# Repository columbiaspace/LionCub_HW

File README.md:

# LionCub_HW
Hardware files for LionCub Satellite, Cubesat Team

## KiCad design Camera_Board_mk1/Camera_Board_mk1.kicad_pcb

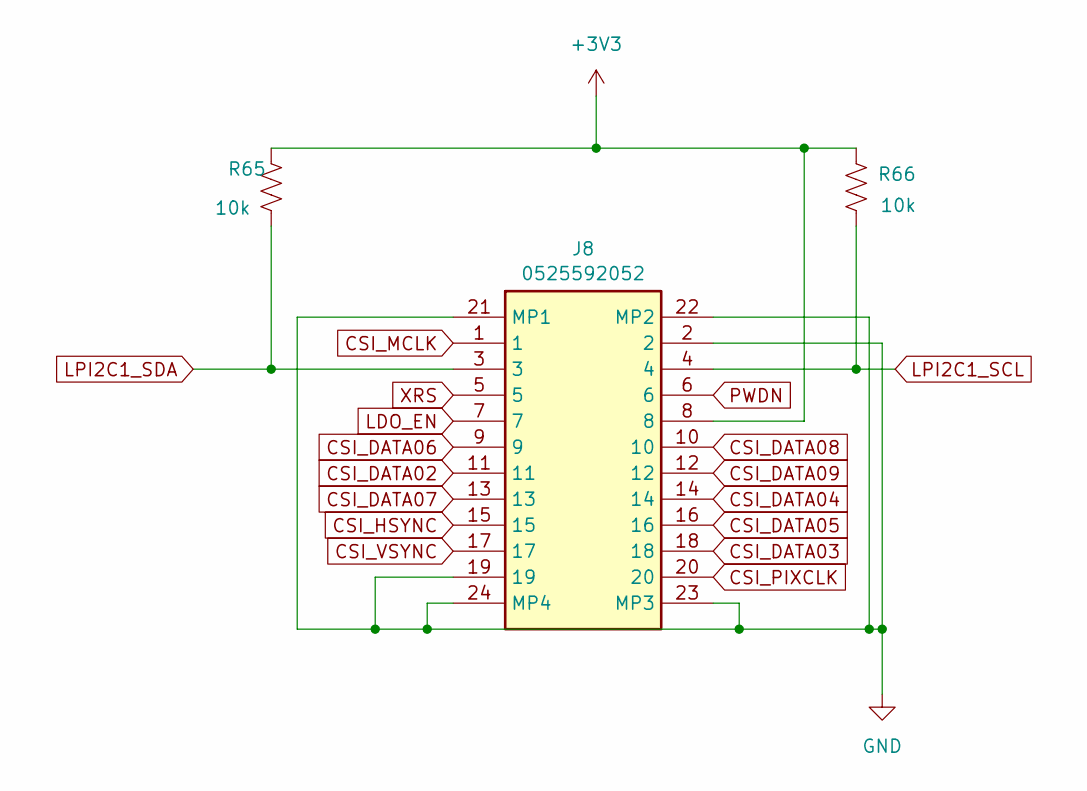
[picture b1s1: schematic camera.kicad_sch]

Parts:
J8: 0525592052; Manufacturer_Part_Number 0525592052‎
R65, R66: 10k; R_0201_0603Metric

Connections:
+3V3: J8.8, R65.1, R66.1; also elsewhere on the board
CSI_DATA02: J8.11; also elsewhere on the board
CSI_DATA03: J8.18; also elsewhere on the board
CSI_DATA04: J8.14; also elsewhere on the board
CSI_DATA05: J8.16; also elsewhere on the board
CSI_DATA06: J8.9; also elsewhere on the board
CSI_DATA07: J8.13; also elsewhere on the board
CSI_DATA08: J8.10; also elsewhere on the board
CSI_DATA09: J8.12; also elsewhere on the board
CSI_HSYNC: J8.15; also elsewhere on the board
CSI_MCLK: J8.1; also elsewhere on the board
CSI_PIXCLK: J8.20; also elsewhere on the board
CSI_VSYNC: J8.17; also elsewhere on the board
GND: J8.2, J8.19, J8.21 (MP1), J8.22 (MP2), J8.23 (MP3), J8.24 (MP4); also elsewhere on the board
LDO_EN: J8.7; also elsewhere on the board
LPI2C1_SCL: J8.4, R66.2; also elsewhere on the board
LPI2C1_SDA: J8.3, R65.2; also elsewhere on the board
PWDN: J8.6; also elsewhere on the board
XRS: J8.5; also elsewhere on the board

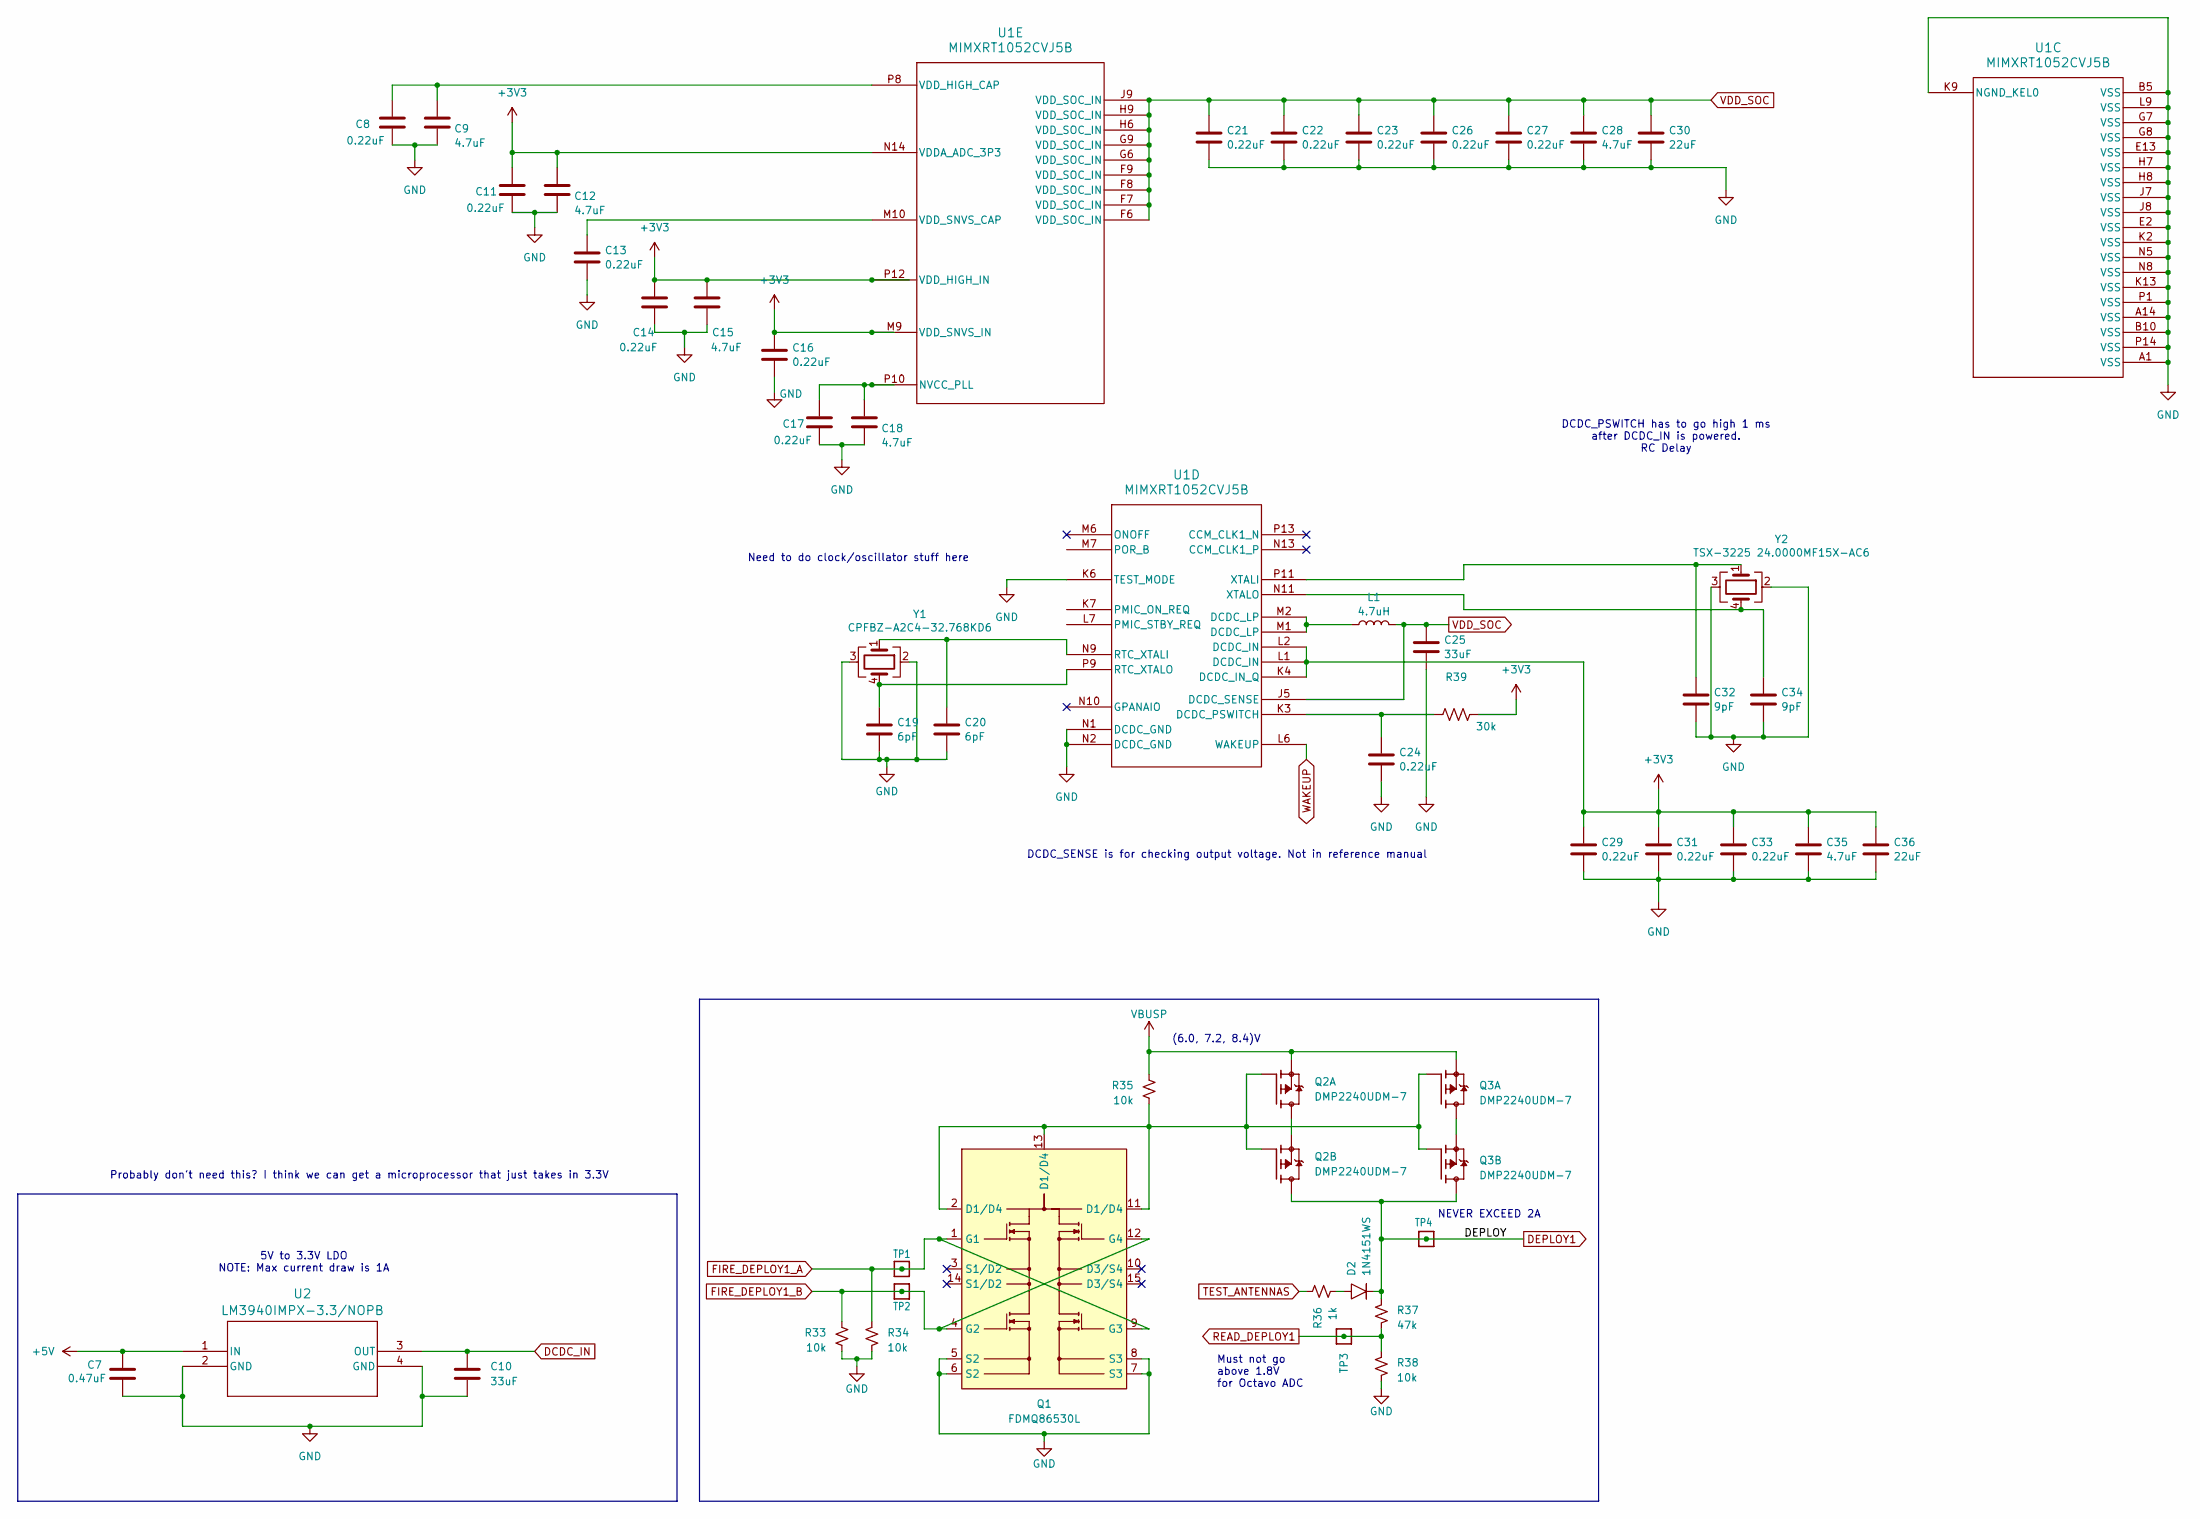
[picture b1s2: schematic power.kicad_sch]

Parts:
C7: 0.47uF; C_0201_0603Metric
C8, C11, C13, C14, C16, C17, C21, C22, C23, C24, C26, C27, C29, C31, C33: 0.22uF; C_0201_0603Metric
C9, C12, C15, C18, C28, C35: 4.7uF; C_0201_0603Metric
C10, C25: 33uF; C_0201_0603Metric
C19, C20: 6pF; C_0201_0603Metric
C30, C36: 22uF; C_0201_0603Metric
C32, C34: 9pF; C_0201_0603Metric
D2: 1N4151WS; D_SOD-323; MPN 1N4151WS-E3-08
L1: 4.7uH; L_0201_0603Metric
Q1: FDMQ86530L; FDMQ8203; MPN FDMQ86530L
Q2, Q3: DMP2240UDM-7; SOT-23-6; MPN DMP2240UDM-7
R33, R34, R35, R38: 10k; R_0201_0603Metric; MPN RMCF0603FT10K0
R36: 1k; R_0201_0603Metric; MPN RMCF0603FT1K00
R37: 47k; R_0201_0603Metric; MPN RMCF0603FT47K0
R39: 30k; R_0201_0603Metric
TP1, TP2, TP3, TP4: Test-Point; TestPoint_Pad_D1.0mm
U1: MIMXRT1052CVJ5B; BGA196C80P14X14_1200X1200X152
U2: LM3940IMPX-3.3/NOPB; MP04A
Y1: CPFBZ-A2C4-32.768KD6; Crystal_SMD_SeikoEpson_MC306-4Pin_8.0x3.2mm
Y2: TSX-3225 24.0000MF15X-AC6; Crystal_SMD_3225-4Pin_3.2x2.5mm

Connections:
+3V3: C11.1, C12.1, C14.1, C15.1, C16.1, C29.1, C31.1, C33.1, C35.1, C36.1, R39.2, U1.K4 (DCDC_IN_Q), U1.L1 (DCDC_IN), U1.L2 (DCDC_IN), U1.M9 (VDD_SNVS_IN), U1.N14 (VDDA_ADC_3P3), U1.P12 (VDD_HIGH_IN); also elsewhere on the board
DCDC_IN: C10.1, U2.3 (OUT); also elsewhere on the board
DEPLOY1: D2.1, Q2.4 (D), Q3.4 (D), R37.1, TP4.1; also elsewhere on the board
FIRE_DEPLOY1_A: Q1.1 (G1), Q1.9 (G3), R34.1, TP1.1; also elsewhere on the board
FIRE_DEPLOY1_B: Q1.4 (G2), Q1.12 (G4), R33.1, TP2.1; also elsewhere on the board
GND: C7.2, C8.2, C9.2, C10.2, C11.2, C12.2, C13.2, C14.2, C15.2, C16.2, C17.2, C18.2, C19.2, C20.2, C21.2, C22.2, C23.2, C24.2, C25.2, C26.2, C27.2, C28.2, C29.2, C30.2, C31.2, C32.2, C33.2, C34.2, C35.2, C36.2, Q1.5 (S2), Q1.6 (S2), Q1.7 (S3), Q1.8 (S3), R33.2, R34.2, R38.2, U1.A1 (VSS), U1.A14 (VSS), U1.B5 (VSS), U1.B10 (VSS), U1.E2 (VSS), U1.E13 (VSS), U1.G7 (VSS), U1.G8 (VSS), U1.H7 (VSS), U1.H8 (VSS), U1.J7 (VSS), U1.J8 (VSS), U1.K2 (VSS), U1.K6 (TEST_MODE), U1.K9 (NGND_KEL0), U1.K13 (VSS), U1.L9 (VSS), U1.N1 (DCDC_GND), U1.N2 (DCDC_GND), U1.N5 (VSS), U1.N8 (VSS), U1.P1 (VSS), U1.P14 (VSS), U2.2 (GND), U2.4 (GND), Y1.2, Y1.3, Y2.2, Y2.3; also elsewhere on the board
unnamed: D2.2, R36.2
unnamed: L1.1, U1.M1 (DCDC_LP), U1.M2 (DCDC_LP)
unnamed: Q2.2 (S), Q2.6 (D)
unnamed: Q1.2 (D1/D4), Q1.11 (D1/D4), Q1.13 (D1/D4), Q2.1 (G), Q2.3 (G), Q3.1 (G), Q3.3 (G), R35.2
unnamed: Q3.2 (S), Q3.6 (D)
unnamed: C24.1, R39.1, U1.K3 (DCDC_PSWITCH)
unnamed: C20.1, U1.N9 (RTC_XTALI), Y1.1
unnamed: C19.1, U1.P9 (RTC_XTALO), Y1.4
unnamed: C32.1, U1.P11 (XTALI), Y2.1
unnamed: C34.1, U1.N11 (XTALO), Y2.4
unnamed: C17.1, C18.1, U1.P10 (NVCC_PLL)
unnamed: C8.1, C9.1, U1.P8 (VDD_HIGH_CAP)
unnamed: C13.1, U1.M10 (VDD_SNVS_CAP)
READ_DEPLOY1: R37.2, R38.1, TP3.1; also elsewhere on the board
TEST_ANTENNAS: R36.1; also elsewhere on the board
VBUS: C7.1, U2.1 (IN); also elsewhere on the board
VBUSP: Q2.5 (S), Q3.5 (S), R35.1; also elsewhere on the board
VDD_SOC: C21.1, C22.1, C23.1, C25.1, C26.1, C27.1, C28.1, C30.1, L1.2, U1.F6 (VDD_SOC_IN), U1.F7 (VDD_SOC_IN), U1.F8 (VDD_SOC_IN), U1.F9 (VDD_SOC_IN), U1.G6 (VDD_SOC_IN), U1.G9 (VDD_SOC_IN), U1.H6 (VDD_SOC_IN), U1.H9 (VDD_SOC_IN), U1.J5 (DCDC_SENSE), U1.J9 (VDD_SOC_IN)
WAKEUP: U1.L6 (WAKEUP)

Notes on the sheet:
DCDC_SENSE is for checking output voltage. Not in reference manual
Need to do clock/oscillator stuff here
Probably don't need this? I think we can get a microprocessor that just takes in 3.3V
Must not go above 1.8V for Octavo ADC
DCDC_PSWITCH has to go high 1 ms after DCDC_IN is powered. RC Delay
5V to 3.3V LDO NOTE: Max current draw is 1A
NEVER EXCEED 2A
(6.0, 7.2, 8.4)V

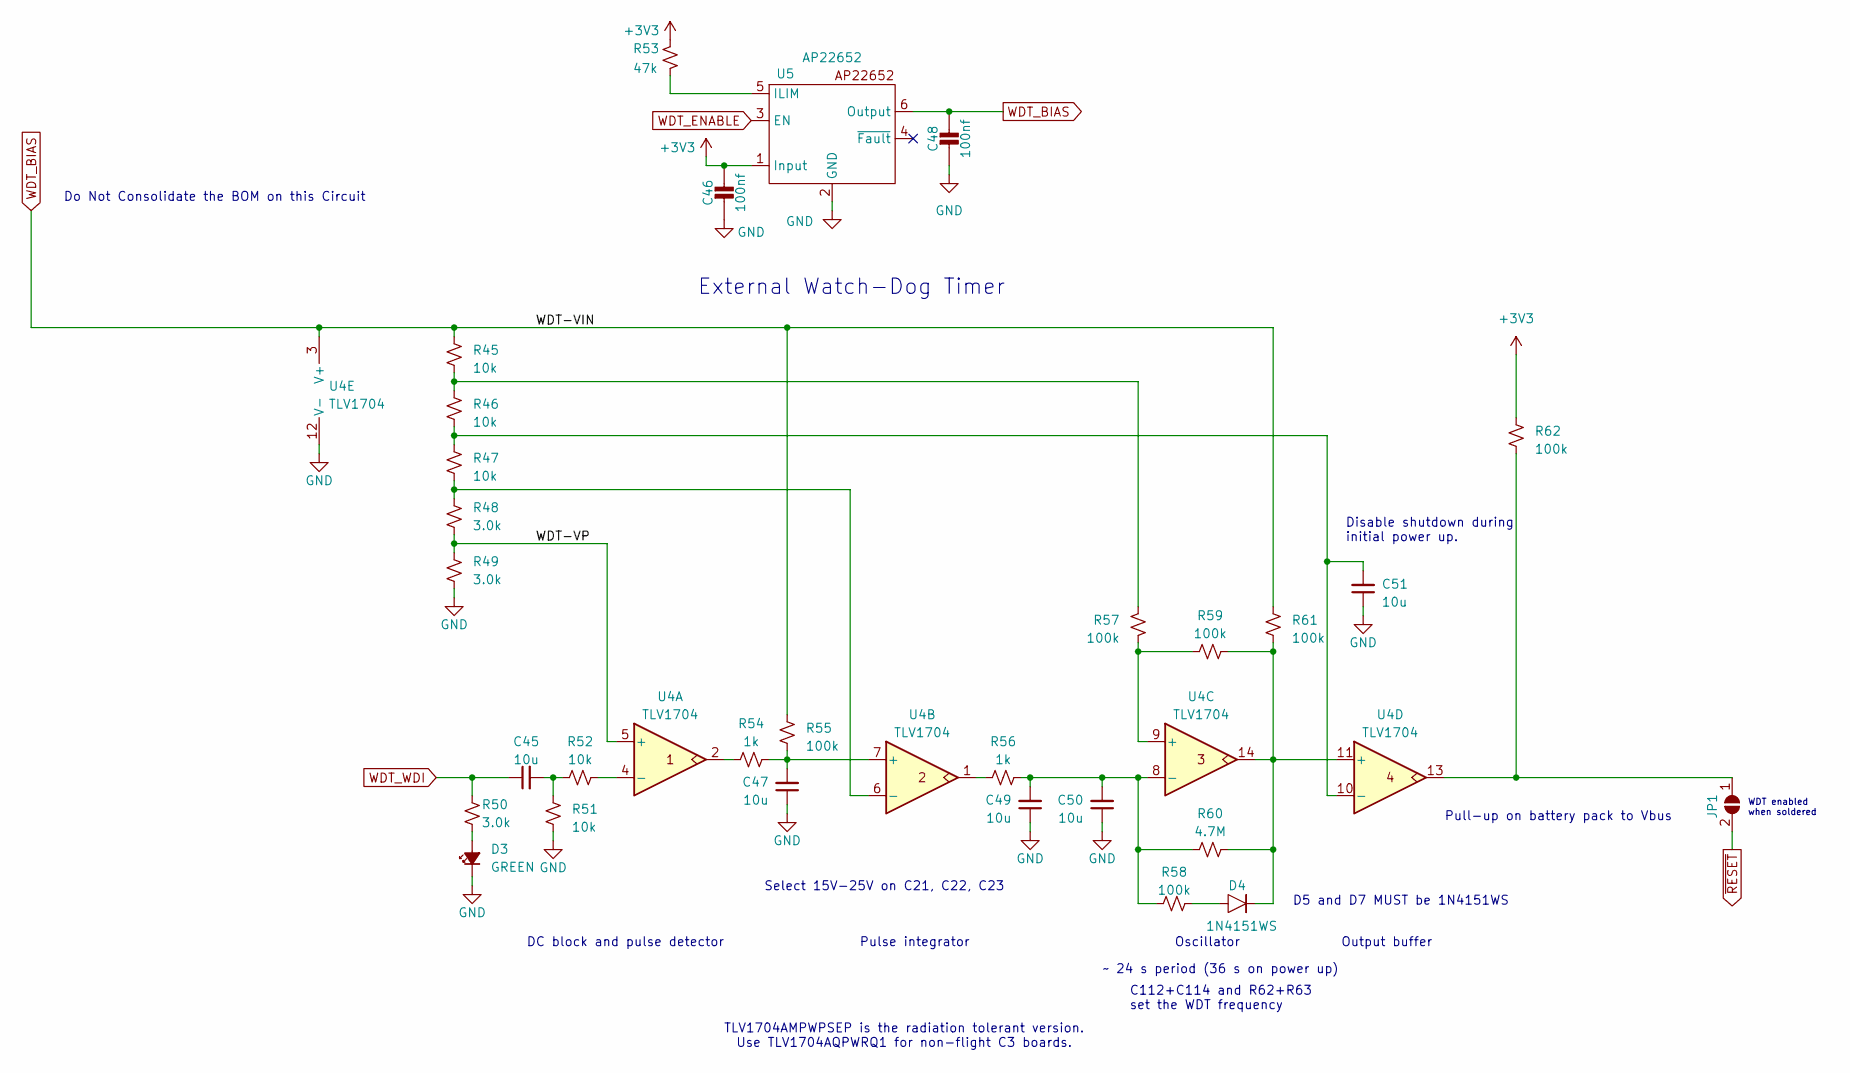
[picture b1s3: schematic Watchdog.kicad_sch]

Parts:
C45, C47, C49, C50, C51: 10u; C_0201_0603Metric; MPN GRT188R61C106KE13D
C46, C48: 100nf; C_0201_0603Metric
D3: GREEN; LED_0603_1608Metric; MPN 150060GS75000
D4: 1N4151WS; D_SOD-323; MPN 1N4151WS-E3-08
JP1: SolderJumper_2_Open; SolderJumper-2_P1.3mm_Open_RoundedPad1.0x1.5mm
R45, R46, R47, R51, R52: 10k; R_0201_0603Metric; MPN RMCF0603FT10K0
R48, R49, R50: 3.0k; R_0201_0603Metric; MPN RMCF0603FT3K00
R53: 47k; R_0201_0603Metric; MPN RMCF0603FT47K0
R54, R56: 1k; R_0201_0603Metric; MPN RMCF0603FT1K00
R55, R57, R58, R59, R61, R62: 100k; R_0201_0603Metric; MPN RMCF0603FT100K
R60: 4.7M; R_0201_0603Metric; MPN RMCF0603FT4M70
U4: TLV1704; TSSOP-14_4.4x5mm_P0.65mm; MPN TLV1704AQPWRQ1
U5: AP22652; SOT95P280X145-6N

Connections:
+3V3: C46.1, R53.1, R62.2, U5.1 (Input); also elsewhere on the board
/Watchdog/WDT-VP: R48.2, R49.1, U4.5 (+)
GND: C46.2, C47.1, C48.2, C49.1, C50.1, C51.1, D3.1 (K), R49.2, R51.2, U4.12 (V-), U5.2 (GND); also elsewhere on the board
unnamed: C45.2, R51.1, R52.1
unnamed: D3.2 (A), R50.2
unnamed: D4.2, R58.1
unnamed: JP1.1 (A), R62.1, U4.13
unnamed: R45.2, R46.1, R57.2
unnamed: R54.1, U4.2
unnamed: R56.1, U4.1
unnamed: R52.2, U4.4 (-)
unnamed: C47.2, R54.2, R55.2, U4.7 (+)
unnamed: R47.2, R48.1, U4.6 (-)
unnamed: R57.1, R59.1, U4.9 (+)
unnamed: C49.2, C50.2, R56.2, R58.2, R60.2, U4.8 (-)
unnamed: D4.1, R59.2, R60.1, R61.1, U4.11 (+), U4.14
unnamed: C51.2, R46.2, R47.1, U4.10 (-)
unnamed: R53.2, U5.5 (ILIM)
WDT_BIAS: C48.1, R45.1, R55.1, R61.2, U4.3 (V+), U5.6 (Output)
WDT_ENABLE: U5.3 (EN); also elsewhere on the board
WDT_WDI: C45.1, R50.1; also elsewhere on the board
~RESET: JP1.2 (B)

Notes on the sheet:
DC block and pulse detector
Output buffer
Select 15V-25V on C21, C22, C23
TLV1704AMPWPSEP is the radiation tolerant version. Use TLV1704AQPWRQ1 for non-flight C3 boards.
External Watch-Dog Timer
Do Not Consolidate the BOM on this Circuit
Pull-up on battery pack to Vbus
Disable shutdown during initial power up.
C112+C114 and R62+R63 set the WDT frequency
WDT enabled when soldered
Pulse integrator
D5 and D7 MUST be 1N4151WS
Oscillator
~ 24 s period (36 s on power up)

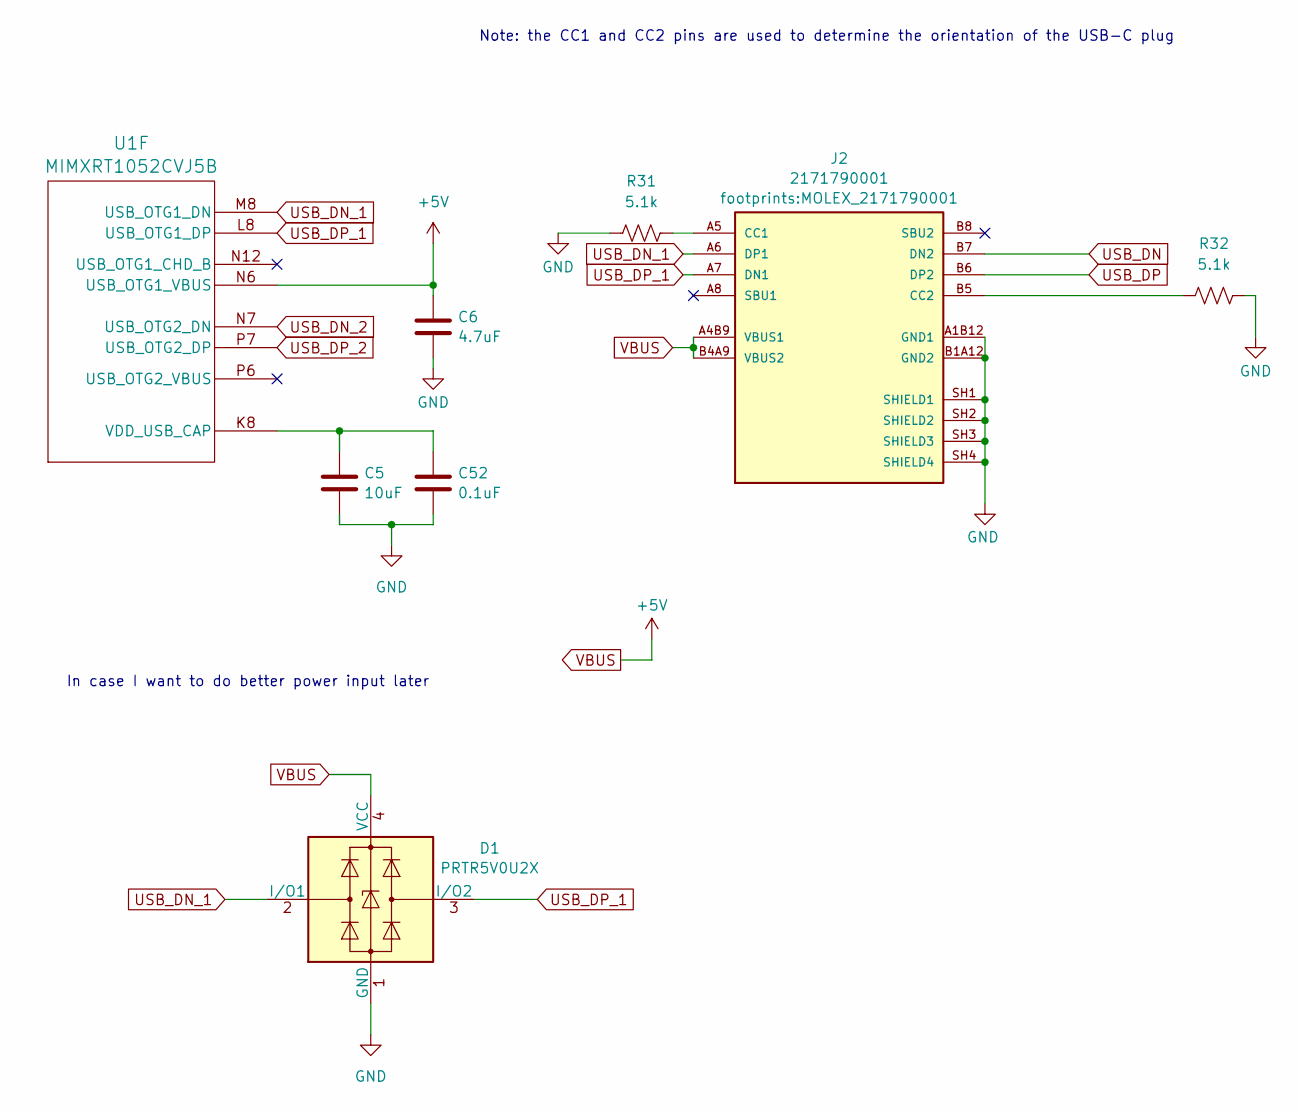
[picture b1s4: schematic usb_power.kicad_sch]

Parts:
C5: 10uF; C_0201_0603Metric
C6: 4.7uF; C_0201_0603Metric
C52: 0.1uF; C_0201_0603Metric
D1: PRTR5V0U2X; SOT-143
J2: 2171790001; MOLEX_2171790001; PARTREV A1
R31, R32: 5.1k; R_0201_0603Metric
U1: MIMXRT1052CVJ5B; BGA196C80P14X14_1200X1200X152

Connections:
GND: C5.2, C6.2, C52.2, D1.1 (GND), J2.A1B12 (GND1), J2.B1A12 (GND2), J2.SH1 (SHIELD1), J2.SH2 (SHIELD2), J2.SH3 (SHIELD3), J2.SH4 (SHIELD4), R31.1, R32.2; also elsewhere on the board
unnamed: J2.A5 (CC1), R31.2
unnamed: J2.B5 (CC2), R32.1
unnamed: C5.1, C52.1, U1.K8 (VDD_USB_CAP)
USB_DN: J2.B7 (DN2)
USB_DN_1: D1.2 (I/O1), J2.A6 (DP1), U1.M8 (USB_OTG1_DN)
USB_DN_2: U1.N7 (USB_OTG2_DN)
USB_DP: J2.B6 (DP2)
USB_DP_1: D1.3 (I/O2), J2.A7 (DN1), U1.L8 (USB_OTG1_DP)
USB_DP_2: U1.P7 (USB_OTG2_DP)
VBUS: C6.1, D1.4 (VCC), J2.A4B9 (VBUS1), J2.B4A9 (VBUS2), U1.N6 (USB_OTG1_VBUS); also elsewhere on the board

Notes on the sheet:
In case I want to do better power input later
Note: the CC1 and CC2 pins are used to determine the orientation of the USB-C plug

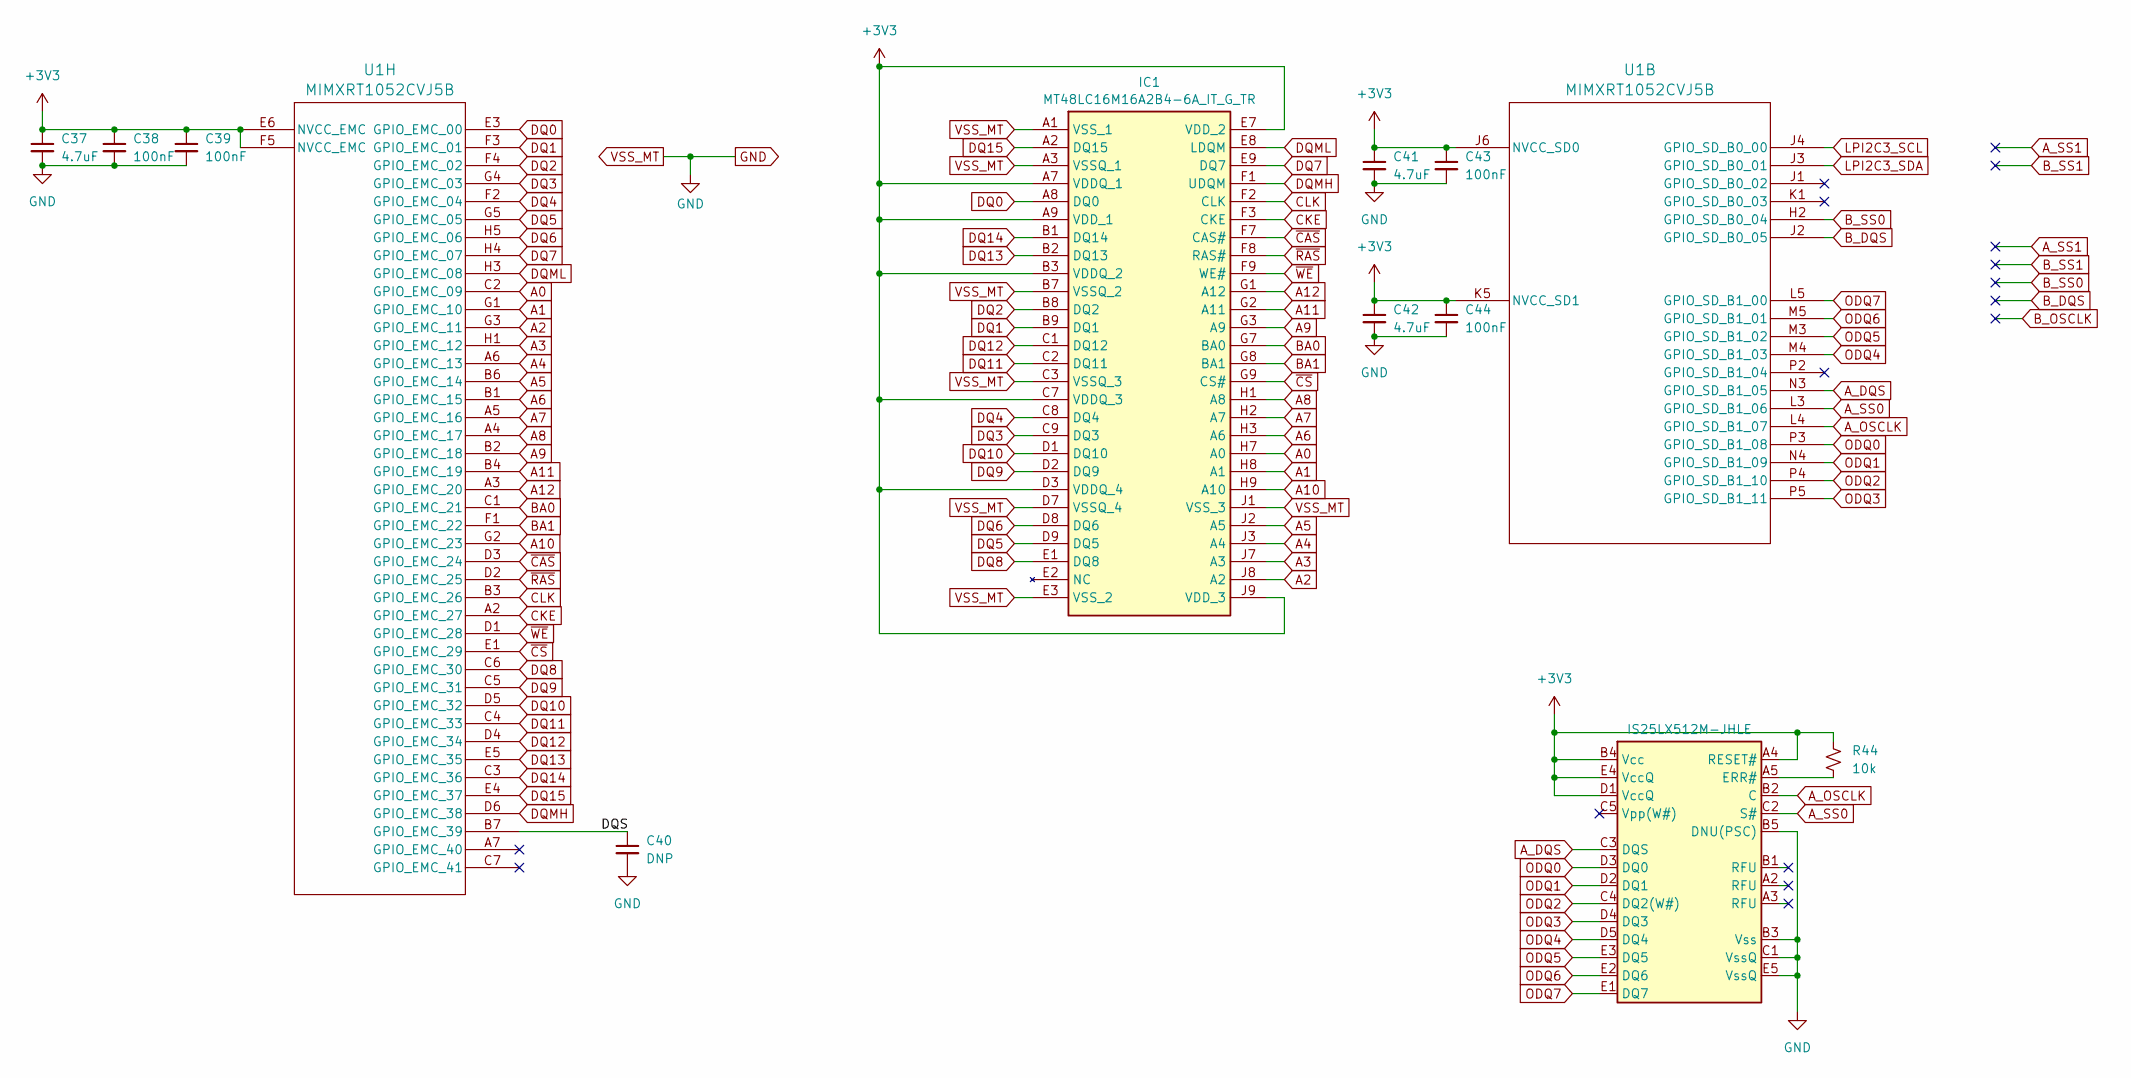
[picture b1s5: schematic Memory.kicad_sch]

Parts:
C37, C41, C42: 4.7uF; C_0201_0603Metric
C38, C39, C43, C44: 100nF; C_0201_0603Metric
C40: DNP; C_0201_0603Metric
IC1: MT48LC16M16A2B4-6A_IT_G_TR; BGA54C80P9X9_800X800X100; Manufacturer_Part_Number MT48LC16M16A2B4-6A IT:G TR; Mouser Part Number 340-128306-REEL
R44: 10k; R_0201_0603Metric
U1: MIMXRT1052CVJ5B; BGA196C80P14X14_1200X1200X152
U3: IS25LX512M-JHLE; BGA24C100P5X5_600X800X120

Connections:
+3V3: C37.1, C38.1, C39.1, C41.1, C42.1, C43.1, C44.1, IC1.A7 (VDDQ_1), IC1.A9 (VDD_1), IC1.B3 (VDDQ_2), IC1.C7 (VDDQ_3), IC1.D3 (VDDQ_4), IC1.E7 (VDD_2), IC1.J9 (VDD_3), R44.1, U1.E6 (NVCC_EMC), U1.F5 (NVCC_EMC), U1.J6 (NVCC_SD0), U1.K5 (NVCC_SD1), U3.A4 (RESET#), U3.B4 (Vcc), U3.D1 (VccQ), U3.E4 (VccQ); also elsewhere on the board
/Memory/DQS: C40.1, U1.B7 (GPIO_EMC_39)
A0: IC1.H7 (A0), U1.C2 (GPIO_EMC_09)
A1: IC1.H8 (A1), U1.G1 (GPIO_EMC_10)
A2: IC1.J8 (A2), U1.G3 (GPIO_EMC_11)
A3: IC1.J7 (A3), U1.H1 (GPIO_EMC_12)
A4: IC1.J3 (A4), U1.A6 (GPIO_EMC_13)
A5: IC1.J2 (A5), U1.B6 (GPIO_EMC_14)
A6: IC1.H3 (A6), U1.B1 (GPIO_EMC_15)
A7: IC1.H2 (A7), U1.A5 (GPIO_EMC_16)
A8: IC1.H1 (A8), U1.A4 (GPIO_EMC_17)
A9: IC1.G3 (A9), U1.B2 (GPIO_EMC_18)
A10: IC1.H9 (A10), U1.G2 (GPIO_EMC_23)
A11: IC1.G2 (A11), U1.B4 (GPIO_EMC_19)
A12: IC1.G1 (A12), U1.A3 (GPIO_EMC_20)
A_DQS: U1.N3 (GPIO_SD_B1_05), U3.C3 (DQS)
A_OSCLK: U1.L4 (GPIO_SD_B1_07), U3.B2 (C)
A_SS0: U1.L3 (GPIO_SD_B1_06), U3.C2 (S#)
BA0: IC1.G7 (BA0), U1.C1 (GPIO_EMC_21)
BA1: IC1.G8 (BA1), U1.F1 (GPIO_EMC_22)
B_DQS: U1.J2 (GPIO_SD_B0_05)
B_SS0: U1.H2 (GPIO_SD_B0_04)
CKE: IC1.F3 (CKE), U1.A2 (GPIO_EMC_27)
CLK: IC1.F2 (CLK), U1.B3 (GPIO_EMC_26)
DQ0: IC1.A8 (DQ0), U1.E3 (GPIO_EMC_00)
DQ1: IC1.B9 (DQ1), U1.F3 (GPIO_EMC_01)
DQ2: IC1.B8 (DQ2), U1.F4 (GPIO_EMC_02)
DQ3: IC1.C9 (DQ3), U1.G4 (GPIO_EMC_03)
DQ4: IC1.C8 (DQ4), U1.F2 (GPIO_EMC_04)
DQ5: IC1.D9 (DQ5), U1.G5 (GPIO_EMC_05)
DQ6: IC1.D8 (DQ6), U1.H5 (GPIO_EMC_06)
DQ7: IC1.E9 (DQ7), U1.H4 (GPIO_EMC_07)
DQ8: IC1.E1 (DQ8), U1.C6 (GPIO_EMC_30)
DQ9: IC1.D2 (DQ9), U1.C5 (GPIO_EMC_31)
DQ10: IC1.D1 (DQ10), U1.D5 (GPIO_EMC_32)
DQ11: IC1.C2 (DQ11), U1.C4 (GPIO_EMC_33)
DQ12: IC1.C1 (DQ12), U1.D4 (GPIO_EMC_34)
DQ13: IC1.B2 (DQ13), U1.E5 (GPIO_EMC_35)
DQ14: IC1.B1 (DQ14), U1.C3 (GPIO_EMC_36)
DQ15: IC1.A2 (DQ15), U1.E4 (GPIO_EMC_37)
DQMH: IC1.F1 (UDQM), U1.D6 (GPIO_EMC_38)
DQML: IC1.E8 (LDQM), U1.H3 (GPIO_EMC_08)
GND: C37.2, C38.2, C39.2, C40.2, C41.2, C42.2, C43.2, C44.2, IC1.A1 (VSS_1), IC1.A3 (VSSQ_1), IC1.B7 (VSSQ_2), IC1.C3 (VSSQ_3), IC1.D7 (VSSQ_4), IC1.E3 (VSS_2), IC1.J1 (VSS_3), U3.B3 (Vss), U3.B5 (DNU(PSC)), U3.C1 (VssQ), U3.E5 (VssQ); also elsewhere on the board
LPI2C3_SCL: U1.J4 (GPIO_SD_B0_00); also elsewhere on the board
LPI2C3_SDA: U1.J3 (GPIO_SD_B0_01); also elsewhere on the board
unnamed: R44.2, U3.A5 (ERR#)
ODQ0: U1.P3 (GPIO_SD_B1_08), U3.D3 (DQ0)
ODQ1: U1.N4 (GPIO_SD_B1_09), U3.D2 (DQ1)
ODQ2: U1.P4 (GPIO_SD_B1_10), U3.C4 (DQ2(W#))
ODQ3: U1.P5 (GPIO_SD_B1_11), U3.D4 (DQ3)
ODQ4: U1.M4 (GPIO_SD_B1_03), U3.D5 (DQ4)
ODQ5: U1.M3 (GPIO_SD_B1_02), U3.E3 (DQ5)
ODQ6: U1.M5 (GPIO_SD_B1_01), U3.E2 (DQ6)
ODQ7: U1.L5 (GPIO_SD_B1_00), U3.E1 (DQ7)
~CAS: IC1.F7 (CAS#), U1.D3 (GPIO_EMC_24)
~CS: IC1.G9 (CS#), U1.E1 (GPIO_EMC_29)
~RAS: IC1.F8 (RAS#), U1.D2 (GPIO_EMC_25)
~WE: IC1.F9 (WE#), U1.D1 (GPIO_EMC_28)

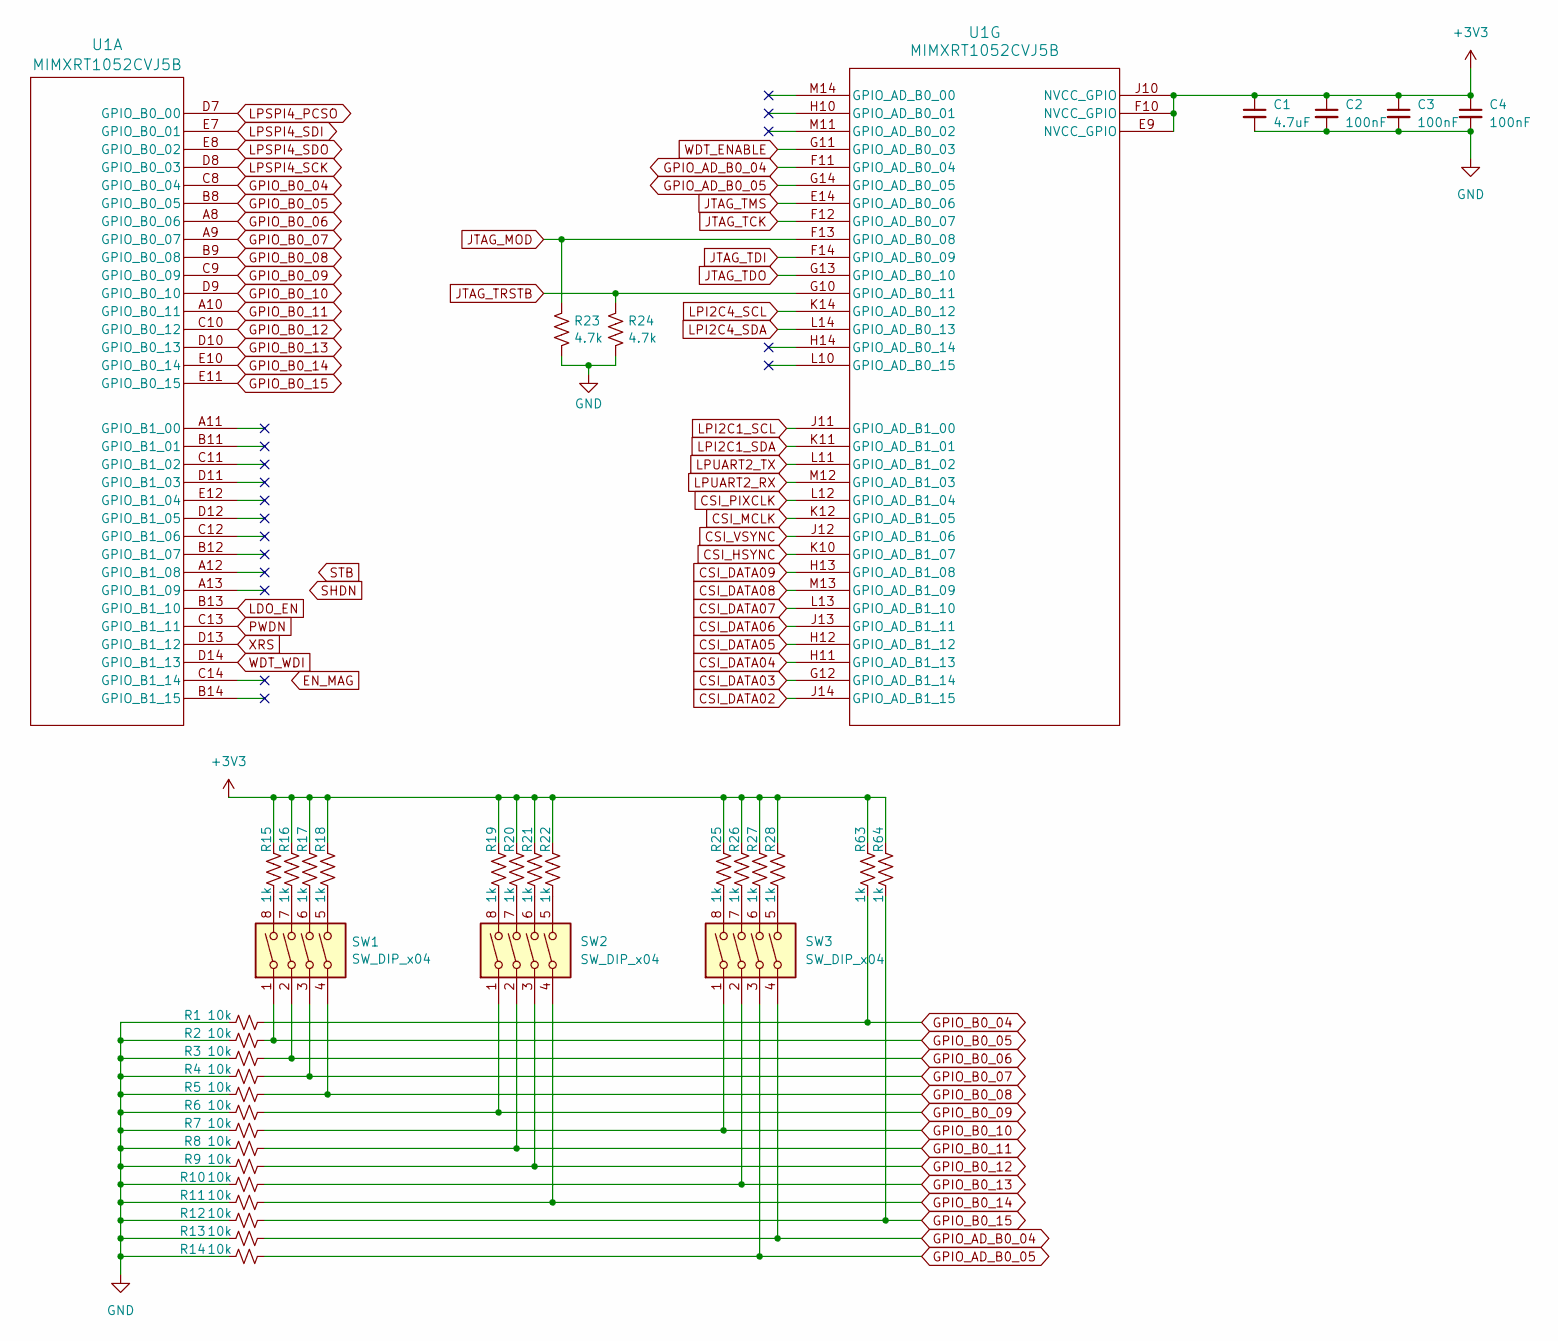
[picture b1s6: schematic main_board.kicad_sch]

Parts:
C1: 4.7uF; C_0201_0603Metric
C2, C3, C4: 100nF; C_0201_0603Metric
R1, R2, R3, R4, R5, R6, R7, R8, R9, R10, R11, R12, R13, R14: 10k; R_0201_0603Metric
R15, R16, R17, R18, R19, R20, R21, R22, R25, R26, R27, R28, R63, R64: 1k; R_0201_0603Metric
R23, R24: 4.7k; R_0201_0603Metric
SW1, SW2, SW3: SW_DIP_x04; SW_DIP_SPSTx04_Slide_Copal_CHS-04A_W5.08mm_P1.27mm_JPin
U1: MIMXRT1052CVJ5B; BGA196C80P14X14_1200X1200X152

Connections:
+3V3: C1.1, C2.1, C3.1, C4.1, R15.1, R16.1, R17.1, R18.1, R19.1, R20.1, R21.1, R22.1, R25.1, R26.1, R27.1, R28.1, R63.1, R64.1, U1.E9 (NVCC_GPIO), U1.F10 (NVCC_GPIO), U1.J10 (NVCC_GPIO); also elsewhere on the board
CSI_DATA02: U1.J14 (GPIO_AD_B1_15); also elsewhere on the board
CSI_DATA03: U1.G12 (GPIO_AD_B1_14); also elsewhere on the board
CSI_DATA04: U1.H11 (GPIO_AD_B1_13); also elsewhere on the board
CSI_DATA05: U1.H12 (GPIO_AD_B1_12); also elsewhere on the board
CSI_DATA06: U1.J13 (GPIO_AD_B1_11); also elsewhere on the board
CSI_DATA07: U1.L13 (GPIO_AD_B1_10); also elsewhere on the board
CSI_DATA08: U1.M13 (GPIO_AD_B1_09); also elsewhere on the board
CSI_DATA09: U1.H13 (GPIO_AD_B1_08); also elsewhere on the board
CSI_HSYNC: U1.K10 (GPIO_AD_B1_07); also elsewhere on the board
CSI_MCLK: U1.K12 (GPIO_AD_B1_05); also elsewhere on the board
CSI_PIXCLK: U1.L12 (GPIO_AD_B1_04); also elsewhere on the board
CSI_VSYNC: U1.J12 (GPIO_AD_B1_06); also elsewhere on the board
GND: C1.2, C2.2, C3.2, C4.2, R1.1, R2.1, R3.1, R4.1, R5.1, R6.1, R7.1, R8.1, R9.1, R10.1, R11.1, R12.1, R13.1, R14.1, R23.2, R24.2; also elsewhere on the board
GPIO_AD_B0_04: R13.2, SW3.4, U1.F11 (GPIO_AD_B0_04)
GPIO_AD_B0_05: R14.2, SW3.3, U1.G14 (GPIO_AD_B0_05)
GPIO_B0_04: R1.2, R63.2, U1.C8 (GPIO_B0_04)
GPIO_B0_05: R2.2, SW1.1, U1.B8 (GPIO_B0_05)
GPIO_B0_06: R3.2, SW1.2, U1.A8 (GPIO_B0_06)
GPIO_B0_07: R4.2, SW1.3, U1.A9 (GPIO_B0_07)
GPIO_B0_08: R5.2, SW1.4, U1.B9 (GPIO_B0_08)
GPIO_B0_09: R6.2, SW2.1, U1.C9 (GPIO_B0_09)
GPIO_B0_10: R7.2, SW3.1, U1.D9 (GPIO_B0_10)
GPIO_B0_11: R8.2, SW2.2, U1.A10 (GPIO_B0_11)
GPIO_B0_12: R9.2, SW2.3, U1.C10 (GPIO_B0_12)
GPIO_B0_13: R10.2, SW3.2, U1.D10 (GPIO_B0_13)
GPIO_B0_14: R11.2, SW2.4, U1.E10 (GPIO_B0_14)
GPIO_B0_15: R12.2, R64.2, U1.E11 (GPIO_B0_15)
JTAG_MOD: R23.1, U1.F13 (GPIO_AD_B0_08); also elsewhere on the board
JTAG_TCK: U1.F12 (GPIO_AD_B0_07); also elsewhere on the board
JTAG_TDI: U1.F14 (GPIO_AD_B0_09); also elsewhere on the board
JTAG_TDO: U1.G13 (GPIO_AD_B0_10); also elsewhere on the board
JTAG_TMS: U1.E14 (GPIO_AD_B0_06); also elsewhere on the board
JTAG_TRSTB: R24.1, U1.G10 (GPIO_AD_B0_11); also elsewhere on the board
LDO_EN: U1.B13 (GPIO_B1_10); also elsewhere on the board
LPI2C1_SCL: U1.J11 (GPIO_AD_B1_00); also elsewhere on the board
LPI2C1_SDA: U1.K11 (GPIO_AD_B1_01); also elsewhere on the board
LPI2C4_SCL: U1.K14 (GPIO_AD_B0_12); also elsewhere on the board
LPI2C4_SDA: U1.L14 (GPIO_AD_B0_13); also elsewhere on the board
LPSPI4_PCSO: U1.D7 (GPIO_B0_00); also elsewhere on the board
LPSPI4_SCK: U1.D8 (GPIO_B0_03); also elsewhere on the board
LPSPI4_SDI: U1.E7 (GPIO_B0_01); also elsewhere on the board
LPSPI4_SDO: U1.E8 (GPIO_B0_02); also elsewhere on the board
LPUART2_RX: U1.M12 (GPIO_AD_B1_03); also elsewhere on the board
LPUART2_TX: U1.L11 (GPIO_AD_B1_02); also elsewhere on the board
unnamed: R15.2, SW1.8
unnamed: R16.2, SW1.7
unnamed: R17.2, SW1.6
unnamed: R18.2, SW1.5
unnamed: R19.2, SW2.8
unnamed: R20.2, SW2.7
unnamed: R21.2, SW2.6
unnamed: R22.2, SW2.5
unnamed: R25.2, SW3.8
unnamed: R26.2, SW3.7
unnamed: R27.2, SW3.6
unnamed: R28.2, SW3.5
PWDN: U1.C13 (GPIO_B1_11); also elsewhere on the board
WDT_ENABLE: U1.G11 (GPIO_AD_B0_03); also elsewhere on the board
WDT_WDI: U1.D14 (GPIO_B1_13); also elsewhere on the board
XRS: U1.D13 (GPIO_B1_12); also elsewhere on the board
